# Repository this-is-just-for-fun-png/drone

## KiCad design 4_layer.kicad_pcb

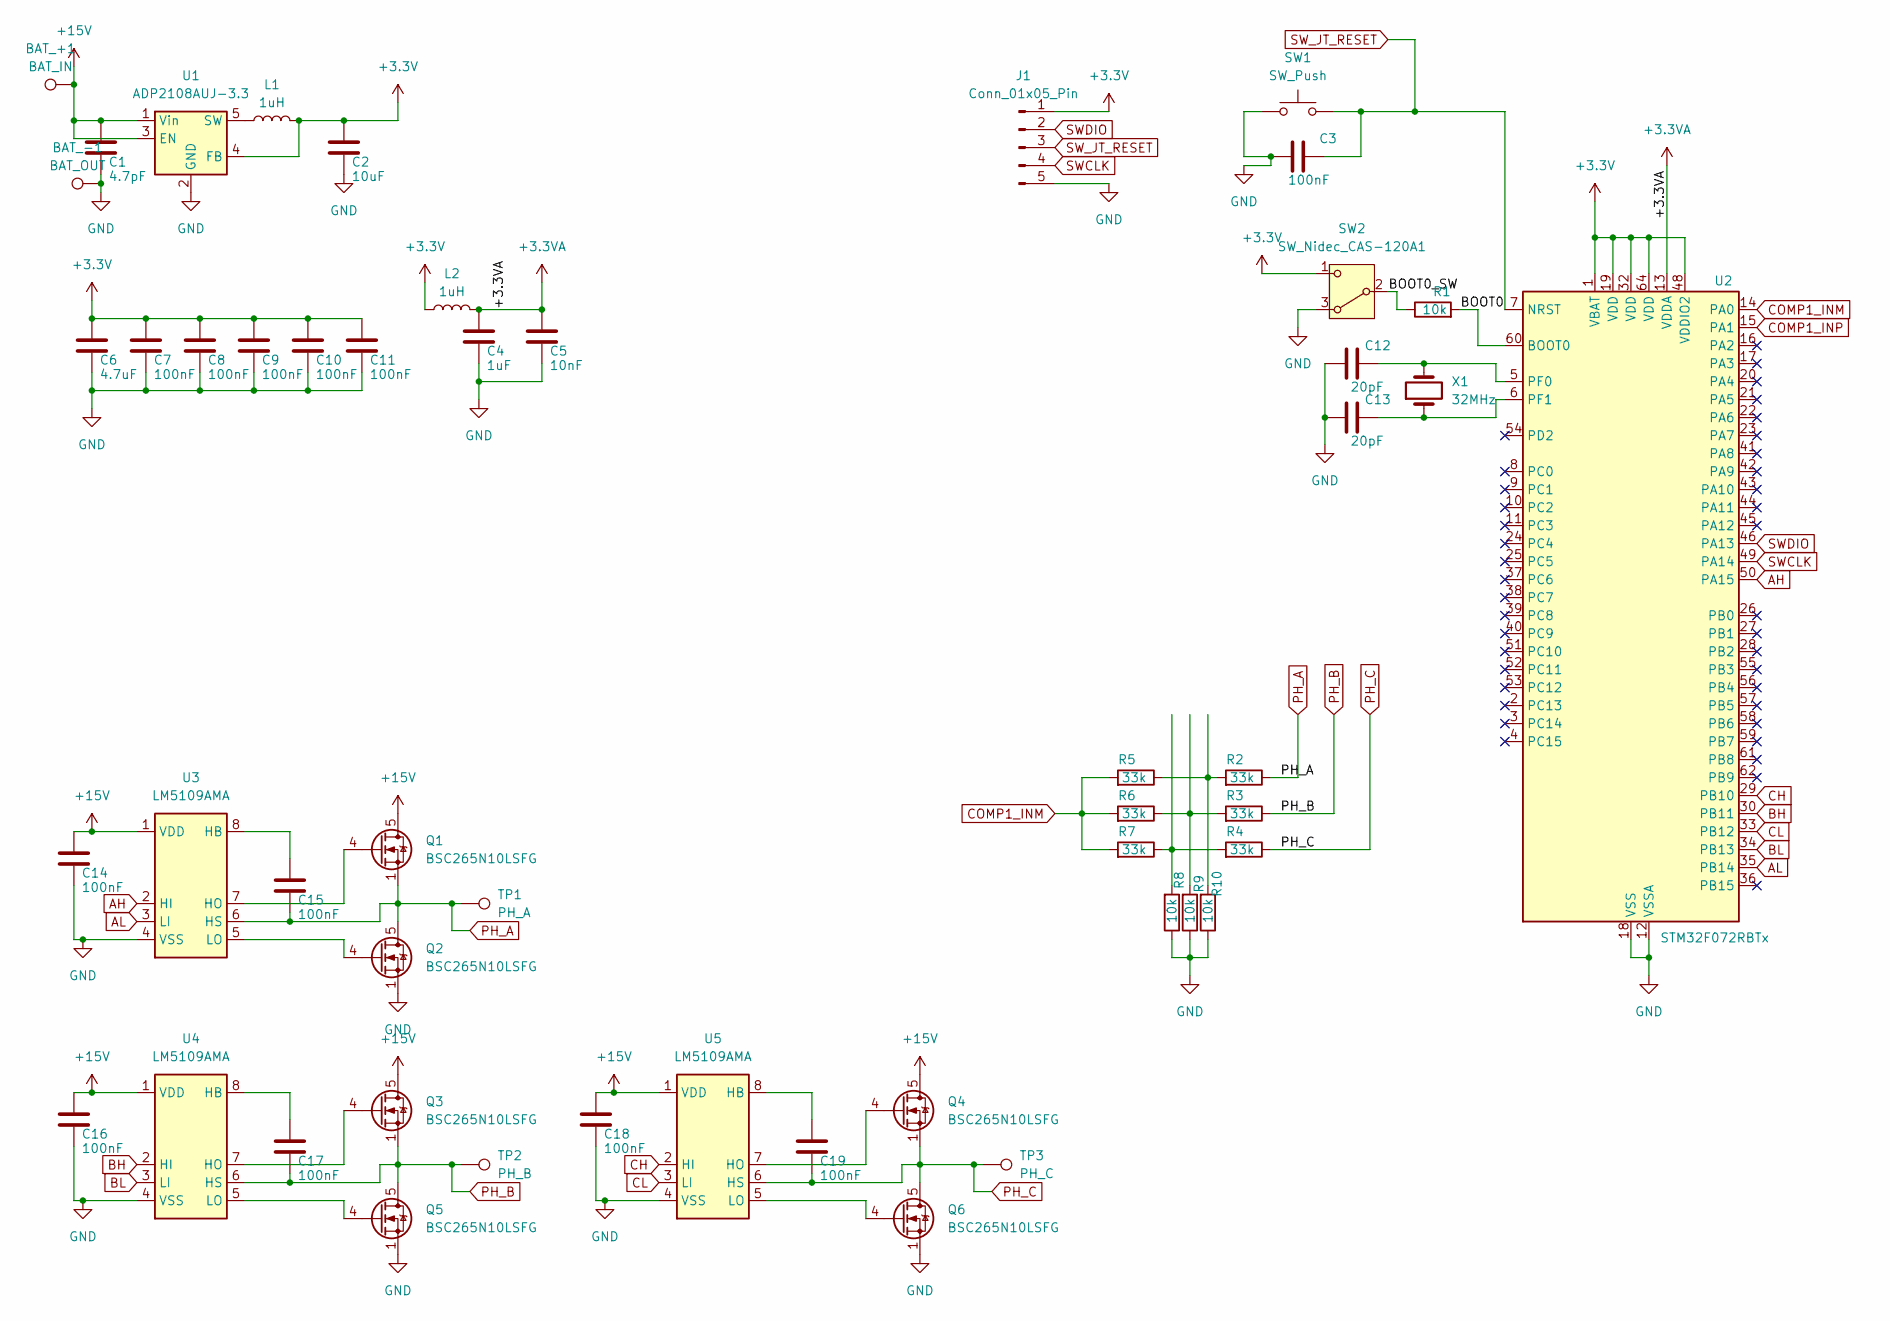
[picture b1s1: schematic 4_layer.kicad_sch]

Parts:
BAT_+1: BAT_IN; SolderWirePad_1x01_SMD_1x2mm
BAT_-1: BAT_OUT; SolderWirePad_1x01_SMD_1x2mm
C1: 4.7pF; C_0402_1005Metric
C2: 10uF; C_0402_1005Metric
C3, C7, C8, C9, C10, C11, C14, C15, C16, C17, C18, C19: 100nF; C_0402_1005Metric
C4: 1uF; C_0402_1005Metric
C5: 10nF; C_0402_1005Metric
C6: 4.7uF; C_0402_1005Metric
C12, C13: 20pF; C_0402_1005Metric
J1: Conn_01x05_Pin; PinHeader_1x05_P1.00mm_Vertical
L1, L2: 1uH; L_0402_1005Metric
Q1, Q2, Q3, Q4, Q5, Q6: BSC265N10LSFG; TDSON-8-1
R1, R8, R9, R10: 10k; R_0402_1005Metric
R2, R3, R4, R5, R6, R7: 33k; R_0402_1005Metric
SW1: SW_Push; SW_Push_1P1T_NO_CK_KMR2
SW2: SW_Nidec_CAS-120A1; Nidec_Copal_CAS-120A
TP1: PH_A; SolderWirePad_1x01_SMD_1x2mm
TP2: PH_B; SolderWirePad_1x01_SMD_1x2mm
TP3: PH_C; SolderWirePad_1x01_SMD_1x2mm
U1: ADP2108AUJ-3.3; TSOT-23-5
U2: STM32F072RBTx; LQFP-64_10x10mm_P0.5mm
U3, U4, U5: LM5109AMA; SOIC-8_3.9x4.9mm_P1.27mm
X1: 32MHz; Crystal_SMD_2012-2Pin_2.0x1.2mm

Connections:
+3.3V: C2.1, C6.1, C7.1, C8.1, C9.1, C10.1, C11.1, J1.1, L1.2, L2.1, SW2.1 (C), U1.4 (FB), U2.1 (VBAT), U2.19 (VDD), U2.32 (VDD), U2.48 (VDDIO2), U2.64 (VDD)
+3.3VA: C4.1, C5.1, L2.2, U2.13 (VDDA)
+15V: BAT_+1.1, C1.1, C14.1, C16.1, C18.1, Q1.5 (D), Q3.5 (D), Q4.5 (D), U1.1 (Vin), U1.3 (EN), U3.1 (VDD), U4.1 (VDD), U5.1 (VDD)
/BOOT0: R1.2, U2.60 (BOOT0)
/BOOT0_SW: R1.1, SW2.2 (B)
AH: U2.50 (PA15), U3.2 (HI)
AL: U2.35 (PB14), U3.3 (LI)
BH: U2.30 (PB11), U4.2 (HI)
BL: U2.34 (PB13), U4.3 (LI)
CH: U2.29 (PB10), U5.2 (HI)
CL: U2.33 (PB12), U5.3 (LI)
COMP1_INM: R5.2, R6.2, R7.2, U2.14 (PA0)
COMP1_INP: U2.15 (PA1)
GND: BAT_-1.1, C1.2, C2.2, C3.1, C4.2, C5.2, C6.2, C7.2, C8.2, C9.2, C10.2, C11.2, C12.1, C13.1, C14.2, C16.2, C18.2, J1.5, Q2.1 (S), Q2.2 (S), Q2.3 (S), Q5.1 (S), Q5.2 (S), Q5.3 (S), Q6.1 (S), Q6.2 (S), Q6.3 (S), R8.1, R9.1, R10.1, SW1.1, SW2.3 (A), U1.2 (GND), U2.12 (VSSA), U2.18 (VSS), U2.31 (VSS), U2.47 (VSS), U2.63 (VSS), U3.4 (VSS), U4.4 (VSS), U5.4 (VSS)
unnamed: Q1.4 (G), U3.7 (HO)
unnamed: Q2.4 (G), U3.5 (LO)
unnamed: Q3.4 (G), U4.7 (HO)
unnamed: Q4.4 (G), U5.7 (HO)
unnamed: Q5.4 (G), U4.5 (LO)
unnamed: Q6.4 (G), U5.5 (LO)
unnamed: R3.2, R6.1, R9.2
unnamed: R4.2, R7.1, R8.2
unnamed: R2.2, R5.1, R10.2
unnamed: L1.1, U1.5 (SW)
unnamed: C12.2, U2.5 (PF0), X1.2
unnamed: C13.2, U2.6 (PF1), X1.1
unnamed: C15.1, U3.8 (HB)
unnamed: C17.1, U4.8 (HB)
unnamed: C19.1, U5.8 (HB)
PH_A: C15.2, Q1.1 (S), Q1.2 (S), Q1.3 (S), Q2.5 (D), R2.1, TP1.1, U3.6 (HS)
PH_B: C17.2, Q3.1 (S), Q3.2 (S), Q3.3 (S), Q5.5 (D), R3.1, TP2.1, U4.6 (HS)
PH_C: C19.2, Q4.1 (S), Q4.2 (S), Q4.3 (S), Q6.5 (D), R4.1, TP3.1, U5.6 (HS)
SWCLK: J1.4, U2.49 (PA14)
SWDIO: J1.2, U2.46 (PA13)
SW_JT_RESET: C3.2, J1.3, SW1.2, U2.7 (NRST)

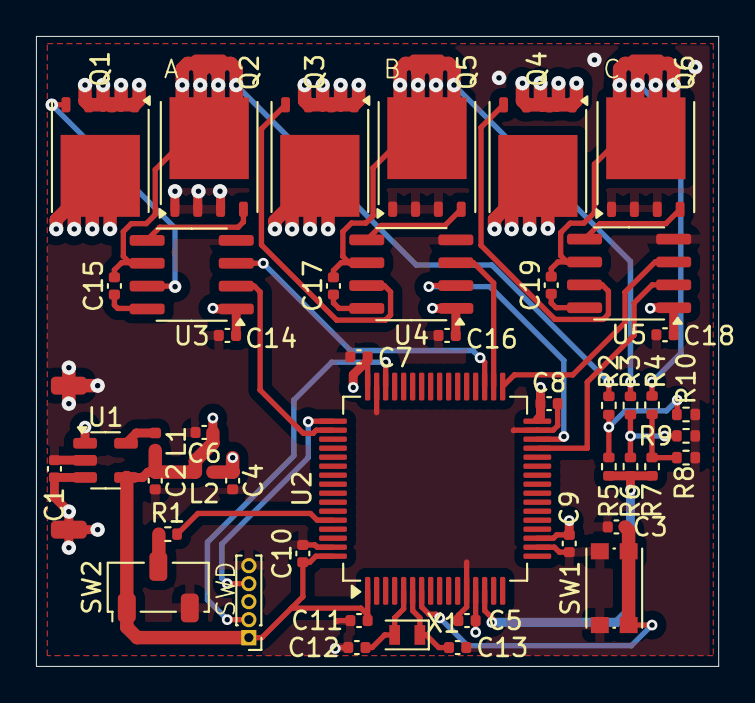
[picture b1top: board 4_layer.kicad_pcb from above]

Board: 4 copper layers, 37.9 x 35.0 mm, 51 parts (0 on the bottom side), 34 nets.
